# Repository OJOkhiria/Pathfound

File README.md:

# Pathfound
A custom PCB controller board and efidget that uses a Xiao RP2040 microcontroller and a MAX7219 IC to increment or decrement your clicks from 0-99 and uses them to turn on LEDS. The Xiao microcontroller provides the logic for the LEDs and the MAX7219. Specifically, by assigning the buttons to inputs on the Xiao (pressed is high and unpressed is low), you can assign high and low values to the LEDs, which are designated as outputs. 

Specifically, pressing Button1 will turn on LED1 (the rightmost one) and increase the counter. If Button2 is pressed within 2 seconds of Button1, LED2 will light up; pressing Button2 also decrements the counter. Button3 turns on LED3 (leftmost LED), but it must be held for at least 800 milliseconds. This minimim hold time also applies to the reset for the counter to allow resetting to be a little more intentional. The controller outputs this counting data to the MAX7219, which uses two seven-segment displays: one for the ones digit, and one for the tens digit. 

 The project schematics and PCB were designed in KiCad, and the firmware was programmed in C++ using the Arduino IDE. I mostly made this project to have something to fidget with on my desk. You can see the demo videos at the link below!

 https://drive.google.com/drive/folders/1nguAO52aBdsrP4bzh1c_a4cOokNBXf4z?usp=drive_link

BOM:

|Reference|Qty|Value|Footprint|Datasheet|
|---------|---|-----|---------|---------|
|AFF1,AFF2|	2	|LTS-6980HR	|Display_7Segment:7SegmentLED_LTS6760_LTS6780|	http://datasheet.octopart.com/LTS-6960HR-Lite-On-datasheet-11803242.pdf|
|C1|	1	|0.1uF|Capacitor_THT:CP_Radial_D10.0mm_P2.50mm| |
|C2|	1	|10uF|Capacitor_THT:CP_Radial_D5.0mm_P2.00mm| |
|D1,D2,D3|	3|	L08R5000Q1|LED:LEDRD254W57D500H1070|	|
|R1,R2,R3|	3|	470|Resistor_THT:R_Axial_DIN0204_L3.6mm_D1.6mm_P5.08mm_Vertical| |
|R4|	1|10k|	Resistor_THT:R_Axial_DIN0204_L3.6mm_D1.6mm_P7.62mm_Horizontal| |
|SW1,SW2,SW3|	3|	SW_Push|	Button_Switch_Keyboard:SW_Cherry_MX_1.00u_PCB| |
|U1|	1|	|	XIAO:XIAO-RP2040-DIP| |
|U2|	1|	MAX7219|				|MAX7219:DIL24	https://datasheets.maximintegrated.com/en/ds/MAX7219-MAX7221.pdf|

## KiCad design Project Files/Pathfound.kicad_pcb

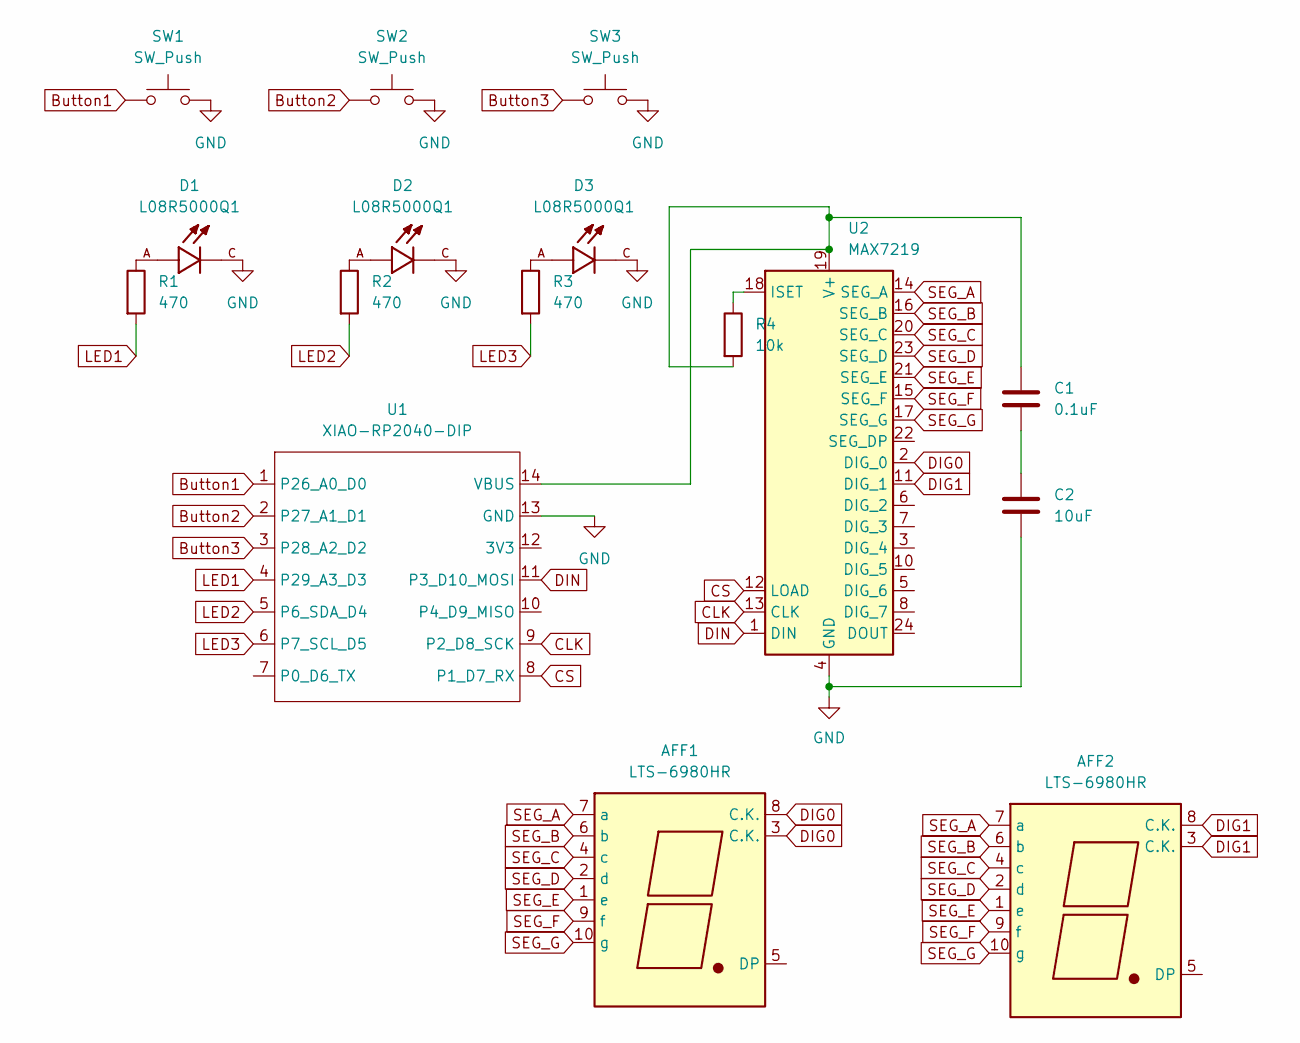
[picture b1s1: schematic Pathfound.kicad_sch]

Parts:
AFF1, AFF2: LTS-6980HR; 7SegmentLED_LTS6760_LTS6780
C1: 0.1uF; CP_Radial_D10.0mm_P2.50mm
C2: 10uF; CP_Radial_D5.0mm_P2.00mm
D1, D2, D3: L08R5000Q1; LEDRD254W57D500H1070; PARTREV NA
R1, R2, R3: 470; R_Axial_DIN0204_L3.6mm_D1.6mm_P5.08mm_Vertical
R4: 10k; R_Axial_DIN0204_L3.6mm_D1.6mm_P7.62mm_Horizontal
SW1, SW2, SW3: SW_Push; SW_Cherry_MX_1.00u_PCB
U1: XIAO-RP2040-DIP
U2: MAX7219; DIL24

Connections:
Button1: SW1.1, U1.1 (P26_A0_D0)
Button2: SW2.1, U1.2 (P27_A1_D1)
Button3: SW3.1, U1.3 (P28_A2_D2)
CLK: U1.9 (P2_D8_SCK), U2.13 (CLK)
CS: U1.8 (P1_D7_RX), U2.12 (LOAD)
DIG0: AFF1.3 (C.K.), AFF1.8 (C.K.), U2.2 (DIG_0)
DIG1: AFF2.3 (C.K.), AFF2.8 (C.K.), U2.11 (DIG_1)
DIN: U1.11 (P3_D10_MOSI), U2.1 (DIN)
GND: C2.2, D1.C, D2.C, D3.C, SW1.2, SW2.2, SW3.2, U1.13 (GND), U2.4 (GND), U2.9 (GND)
LED1: R1.2, U1.4 (P29_A3_D3)
LED2: R2.2, U1.5 (P6_SDA_D4)
LED3: R3.2, U1.6 (P7_SCL_D5)
unnamed: C1.2, C2.1
unnamed: D1.A, R1.1
unnamed: D2.A, R2.1
unnamed: D3.A, R3.1
unnamed: C1.1, R4.2, U1.14 (VBUS), U2.19 (V+)
unnamed: R4.1, U2.18 (ISET)
SEG_A: AFF1.7 (a), AFF2.7 (a), U2.14 (SEG_A)
SEG_B: AFF1.6 (b), AFF2.6 (b), U2.16 (SEG_B)
SEG_C: AFF1.4 (c), AFF2.4 (c), U2.20 (SEG_C)
SEG_D: AFF1.2 (d), AFF2.2 (d), U2.23 (SEG_D)
SEG_E: AFF1.1 (e), AFF2.1 (e), U2.21 (SEG_E)
SEG_F: AFF1.9 (f), AFF2.9 (f), U2.15 (SEG_F)
SEG_G: AFF1.10 (g), AFF2.10 (g), U2.17 (SEG_G)

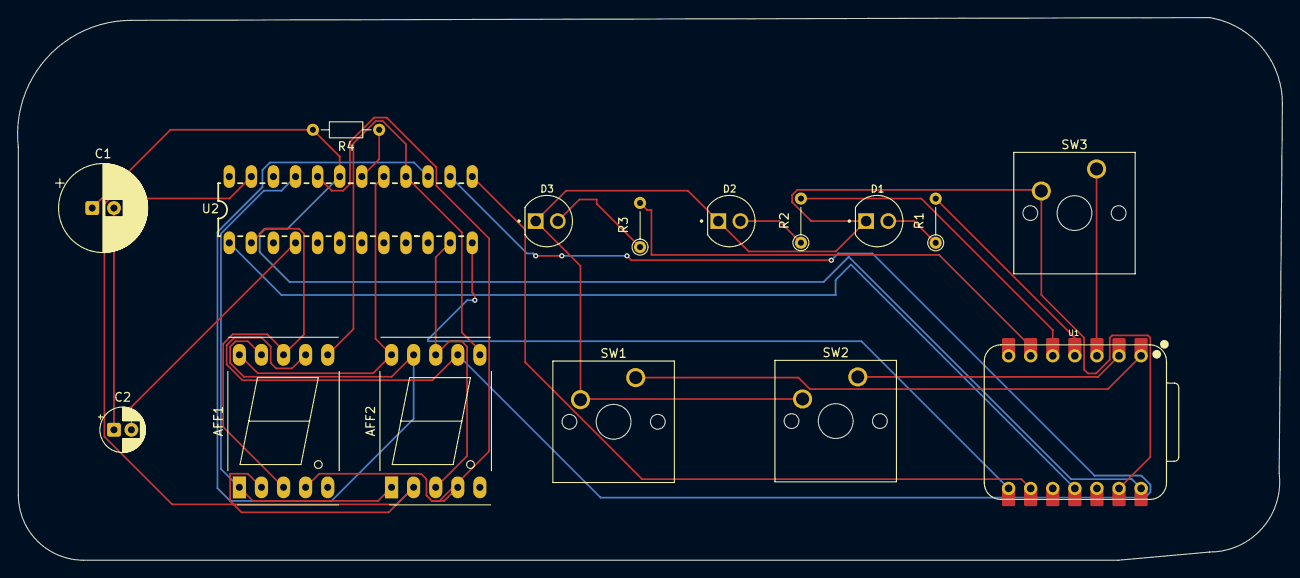
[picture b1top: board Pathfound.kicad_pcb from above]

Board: 2 copper layers, 145.5 x 62.4 mm, 16 parts (0 on the bottom side), 25 nets.

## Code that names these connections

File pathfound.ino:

#include <Arduino.h>

const int BUT1 = D0;  // Increment
const int BUT2 = D1;  // Decrement
const int BUT3 = D2;  // Reset (hold 800 ms)

const int LED1 = D3;
const int LED2 = D4;
const int LED3 = D5;

const int DIN_PIN = D10;
const int CLK_PIN = D8;
const int CS_PIN  = D7;

int count = 0;

// Increment debounce
int lastIncReading = HIGH;
int incState = HIGH;
unsigned long lastIncDebounceTime = 0;

// Decrement debounce
int lastDecReading = HIGH;
int decState = HIGH;
unsigned long lastDecDebounceTime = 0;

const unsigned long debounceDelay = 50;

// Timing variables
unsigned long lastBut1Time = 0;
unsigned long lastBut2Time = 0;
unsigned long but3PressStart = 0;

bool resetPerformed = false;

void sendToMax7219(uint8_t opcode, uint8_t data) {
  digitalWrite(CS_PIN, LOW);
  shiftOut(DIN_PIN, CLK_PIN, MSBFIRST, opcode);
  shiftOut(DIN_PIN, CLK_PIN, MSBFIRST, data);
  digitalWrite(CS_PIN, HIGH);
}

void initDisplay() {
  pinMode(DIN_PIN, OUTPUT);
  pinMode(CLK_PIN, OUTPUT);
  pinMode(CS_PIN, OUTPUT);

  digitalWrite(DIN_PIN, LOW);
  digitalWrite(CLK_PIN, LOW);
  digitalWrite(CS_PIN, HIGH);

  sendToMax7219(0x0F, 0x00);
  sendToMax7219(0x0C, 0x01);
  sendToMax7219(0x0B, 0x01);
  sendToMax7219(0x09, 0xFF);
  sendToMax7219(0x0A, 0x08);

  sendToMax7219(1, 0x0F);
  sendToMax7219(2, 0x0F);
}

void clearDisplay() {
  sendToMax7219(1, 0x0F);
  sendToMax7219(2, 0x0F);
}

void showStartupTest() {
  sendToMax7219(1, 8);
  sendToMax7219(2, 8);
  delay(500);

  sendToMax7219(1, 1);
  sendToMax7219(2, 2);
  delay(500);

  clearDisplay();
}

void displayCount(int value) {
  value = constrain(value, 0, 99);

  uint8_t tens = value / 10;
  uint8_t ones = value % 10;

  if (value < 10) {
    sendToMax7219(1, 0x0F);
  } else {
    sendToMax7219(1, tens);
  }

  sendToMax7219(2, ones);
}

void setup() {
  pinMode(BUT1, INPUT_PULLUP);
  pinMode(BUT2, INPUT_PULLUP);
  pinMode(BUT3, INPUT_PULLUP);

  pinMode(LED1, OUTPUT);
  pinMode(LED2, OUTPUT);
  pinMode(LED3, OUTPUT);

  initDisplay();
  showStartupTest();
  displayCount(count);
}

void loop() {
  unsigned long now = millis();

  int but1Reading = digitalRead(BUT1);
  int but2Reading = digitalRead(BUT2);
  int but3Reading = digitalRead(BUT3);

  // LED1 and LED2 follow button presses
  digitalWrite(LED1, but1Reading == LOW);
  digitalWrite(LED2, but2Reading == LOW);

  // --------------------
  // BUT3 hold-to-reset
  // --------------------
  if (but3Reading == LOW) {
    if (but3PressStart == 0) {
      but3PressStart = now;
      resetPerformed = false;
    }

    if ((now - but3PressStart) >= 800) {
      digitalWrite(LED3, HIGH);

      if (!resetPerformed) {
        count = 0;
        displayCount(count);
        resetPerformed = true;
      }
    } else {
      digitalWrite(LED3, LOW);
    }
  } else {
    but3PressStart = 0;
    resetPerformed = false;
    digitalWrite(LED3, LOW);
  }

  // --------------------
  // Increment (BUT1)
  // --------------------
  if (but1Reading != lastIncReading) {
    lastIncDebounceTime = now;
  }

  if ((now - lastIncDebounceTime) > debounceDelay) {
    if (but1Reading != incState) {
      incState = but1Reading;

      if (incState == LOW) {
        count = (count + 1) % 100;
        displayCount(count);
        lastBut1Time = now;
      }
    }
  }

  lastIncReading = but1Reading;

  // --------------------
  // Decrement (BUT2)
  // --------------------
  if (but2Reading != lastDecReading) {
    lastDecDebounceTime = now;
  }

  if ((now - lastDecDebounceTime) > debounceDelay) {
    if (but2Reading != decState) {
      decState = but2Reading;

      if (decState == LOW) {
        if (count > 0) {
          count--;
        } else {
          count = 99;
        }

        displayCount(count);
        lastBut2Time = now;
      }
    }
  }

  lastDecReading = but2Reading;

  // --------------------
  // LED2 bonus indicator
  // --------------------
  unsigned long diff =
      (lastBut1Time > lastBut2Time)
          ? (lastBut1Time - lastBut2Time)
          : (lastBut2Time - lastBut1Time);

  if (lastBut1Time != 0 &&
      lastBut2Time != 0 &&
      diff <= 2000) {
    digitalWrite(LED2, HIGH);
  }
}

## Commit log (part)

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2026-06-01 Add g.gitkeep to Project Files directory
2026-06-15 Refactor BOM section to use Markdown table format
    Updated BOM table format to Markdown style.
2026-06-16 Format BOM table in README.md
2026-06-16 Enhance README with detailed button functionality
    Expanded the description of button functionalities and clarified the project details.
2026-06-16 Fix grammatical error in README description
    Corrected verb agreement in project description.
2026-06-16 Enhance README with demo links and images
    Added demo video links and images to README.
